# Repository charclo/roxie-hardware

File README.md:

# Welcome
This repository contains the kicad and gerber files for the open source Roxie (based on the no longer maintained [DAVEga OS](https://github.com/janpom/davega)).
# Building instructions
Instructions on how to order and make your own Roxie display can be found [here](https://github.com/charclo/roxie-hardware/wiki)
# Photos

## License

Roxie firmware and hardware design is released under [GNU GPL v3](https://github.com/charclo/roxie-firmware/blob/master/LICENSE).

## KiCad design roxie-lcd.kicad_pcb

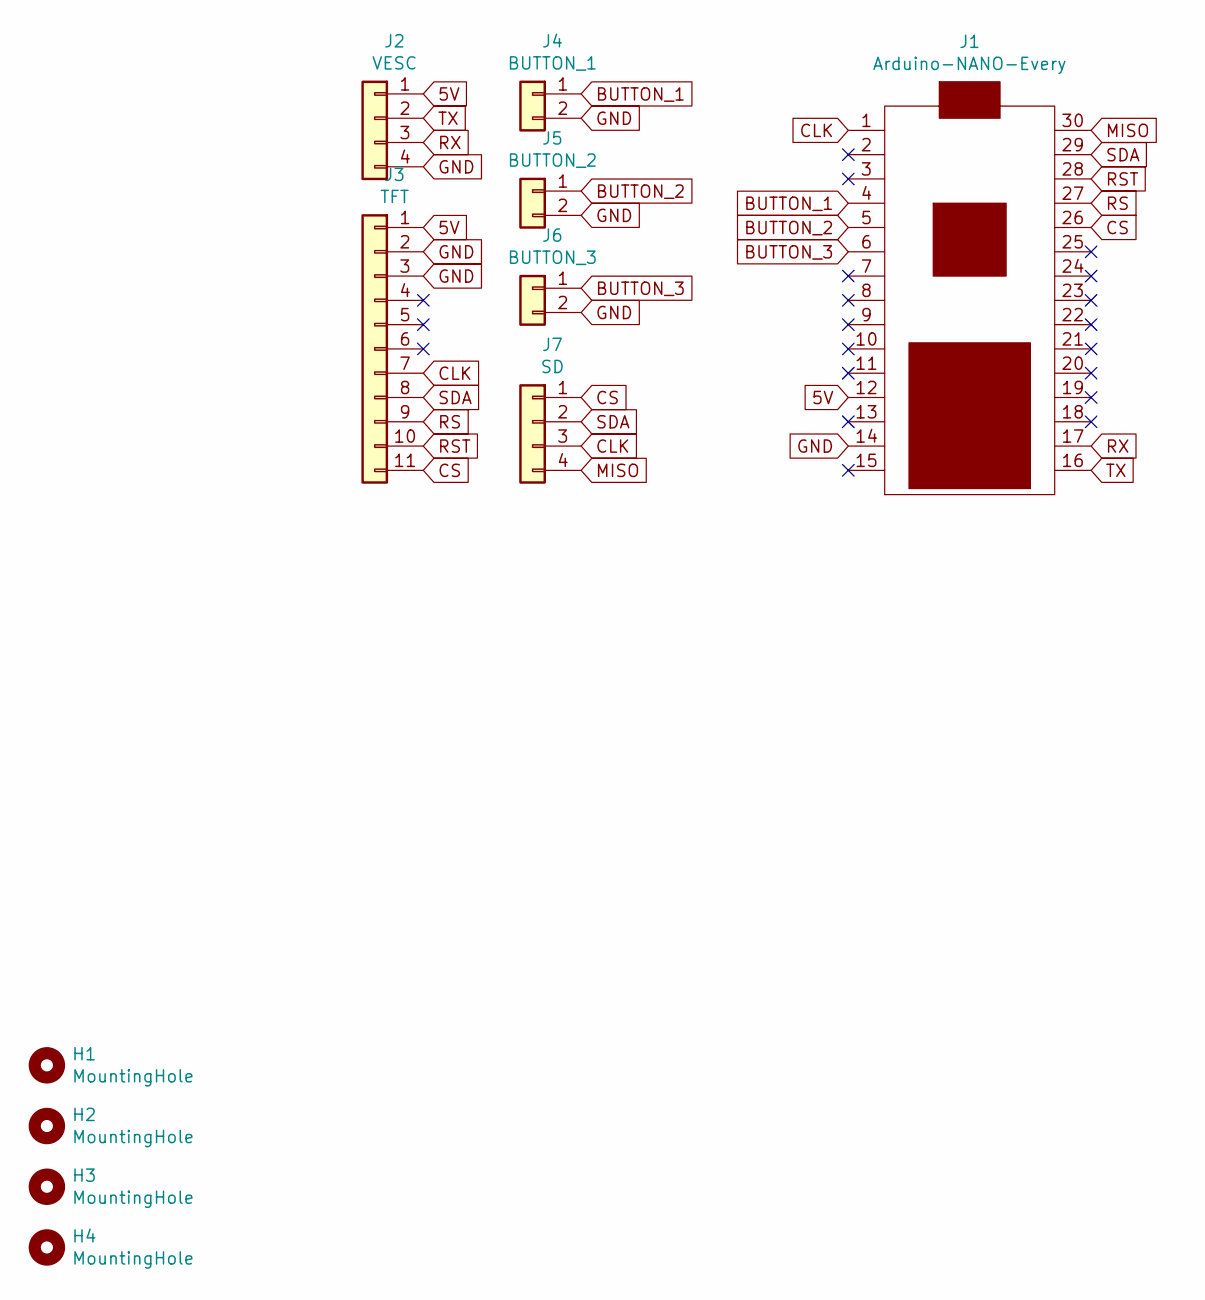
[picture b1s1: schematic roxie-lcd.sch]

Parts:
H1, H2, H3, H4: MountingHole; MountingHole_3.2mm_M3_ISO7380
J1: Arduino-NANO-Every; NANO_33_Footprint_SMD_Castell
J2: VESC; JST_PH_B4B-PH-K_1x04_P2.00mm_Vertical
J3: TFT; PinHeader_1x11_P2.54mm_Vertical
J4: BUTTON_1; PinHeader_1x02_P2.54mm_Vertical
J5: BUTTON_2; PinHeader_1x02_P2.54mm_Vertical
J6: BUTTON_3; PinHeader_1x02_P2.54mm_Vertical
J7: SD; PinHeader_1x04_P2.54mm_Vertical

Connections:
5V: J1.12, J2.1, J3.1
BUTTON_1: J1.4, J4.1
BUTTON_2: J1.5, J5.1
BUTTON_3: J1.6, J6.1
CLK: J1.1, J3.7, J7.3
CS: J1.26, J3.11, J7.1
GND: J1.14, J2.4, J3.2, J3.3, J4.2, J5.2, J6.2
MISO: J1.30, J7.4
RS: J1.27, J3.9
RST: J1.28, J3.10
RX: J1.17, J2.3
SDA: J1.29, J3.8, J7.2
TX: J1.16, J2.2

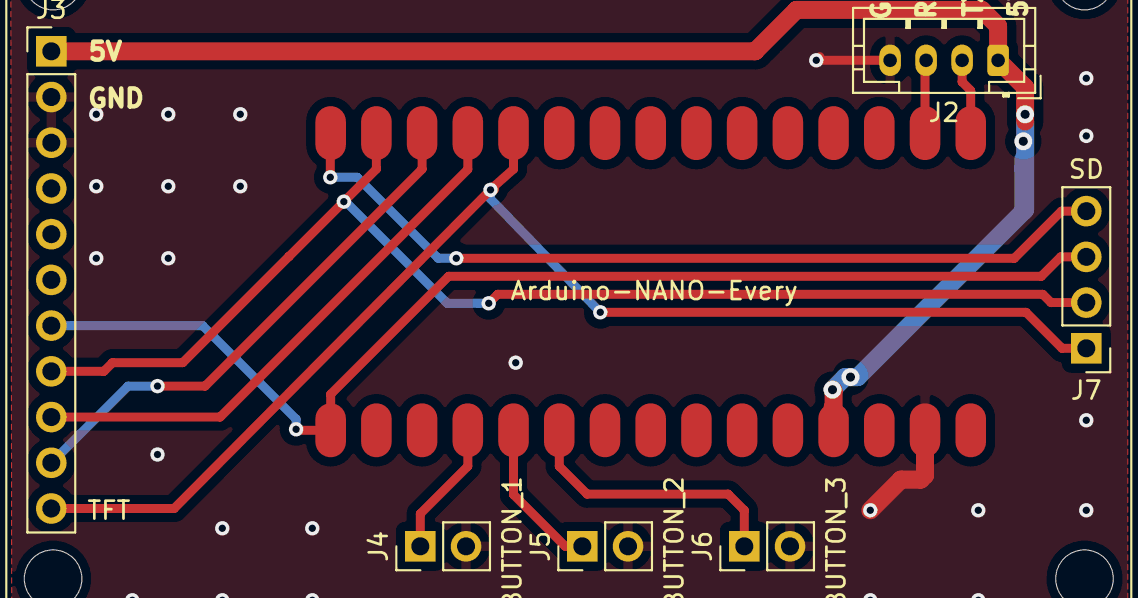
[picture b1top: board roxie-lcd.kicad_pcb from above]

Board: 2 copper layers, 11 parts (0 on the bottom side), 13 nets.

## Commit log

2020-07-17 changed button position
2020-07-17 changed some positions
2020-07-22 pcb designed
2020-07-22 changed position of connectors
2020-07-27 first finished version
2020-07-28 positioning almost correct
2020-07-28 some small adjustments, rotated the sd card connector
2020-07-30 added mountingholes on pcb, added PDF's of schematic and PCB
2020-08-07 small stuff
2020-08-07 added readme
2020-11-19 Added photos
2020-11-20 added screenshots
2020-11-20 Changed VESC connector to PH and added SD card support
